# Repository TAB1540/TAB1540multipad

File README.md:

# TAB1540multipad

TAB1540multipad is a 9 key macropad with 1 rotary encoder, an OLED Display. It also has 4 WS2812B Leds, and uses KMK firmware.

## Features

- Basic abs 3d printable case
- 128x32 OLED Display
- 1 EC11 Rotary encoder for spinning around
- 4 WS2812B RGB LEDs.
- 9 keys

## CAD demo

Everything fits together using 4 M3 Bolts. 
Case is made from 2 parts.

Designed using freeCAD 1.0.1 (first time for me)
## PCB

This is my PCB, which was made in KiCad.

PCB

Schematic

## Firmware Overview

This hackpad uses KMK firmware for maybe everything

- The rotary encoder changes volume. press do nothing
- The 9 keys is just keys
- The OLED is something I forgor

## BOM:

Here should be everything you need to make this hackpad

- 9x Cherry MX Switches
- 9x DSA Keycaps
- 4x M3x16mm SHCS Bolts
- 9x 1N4148 DO-35 Diodes.
- 4x WS2812B LEDs
- 1x 0.91" 128x32 OLED Display
- 1x EC11 Rotary Encoder
- 1x XIAO RP2040
- 1x Case (2 printed parts)
## Extra

This is another version of this project

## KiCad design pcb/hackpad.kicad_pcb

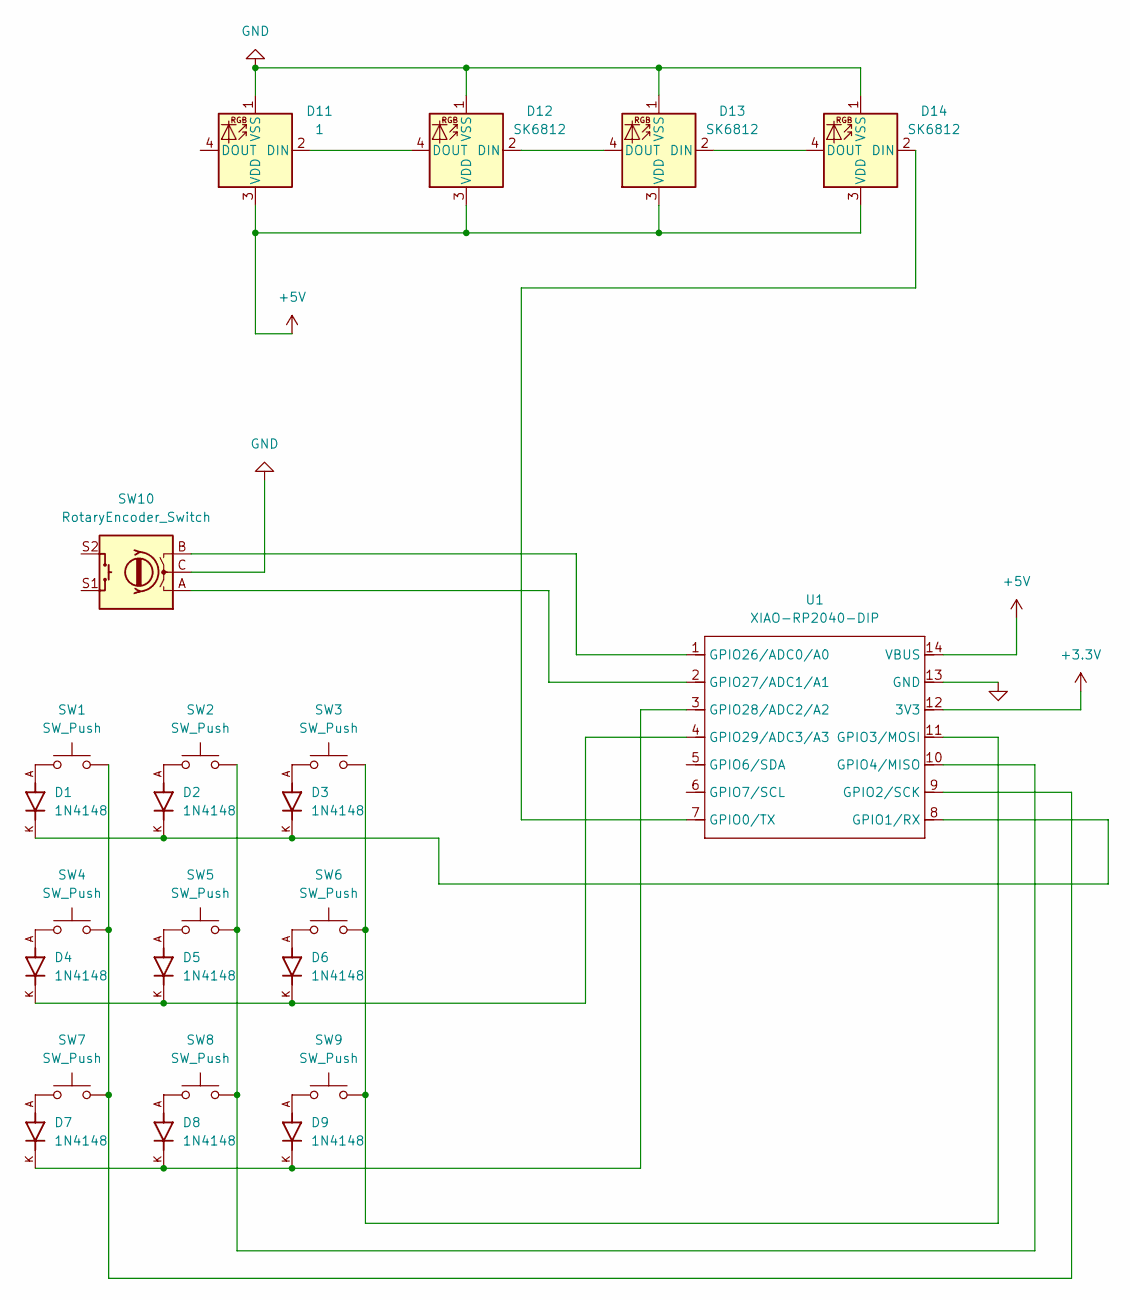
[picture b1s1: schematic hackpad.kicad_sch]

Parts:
D1, D2, D3, D4, D5, D6, D7, D8, D9: 1N4148; DIOAD753W49L380D172B; PARTREV 5
D11: 1; LED_SK6812MINI_PLCC4_3.5x3.5mm_P1.75mm
D12, D13, D14: SK6812; LED_SK6812MINI_PLCC4_3.5x3.5mm_P1.75mm
SW1, SW2, SW3, SW4, SW5, SW6, SW7, SW8, SW9: SW_Push; SW_Cherry_MX_1.00u_PCB
SW10: RotaryEncoder_Switch
U1: XIAO-RP2040-DIP

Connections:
+3.3V: U1.12 (3V3)
+5V: D11.3 (VDD), D12.3 (VDD), D13.3 (VDD), D14.3 (VDD), U1.14 (VBUS)
GND: D11.1 (VSS), D12.1 (VSS), D13.1 (VSS), D14.1 (VSS), SW10.C, U1.13 (GND)
unnamed: D1.A, SW1.1
unnamed: D2.A, SW2.1
unnamed: D3.A, SW3.1
unnamed: D4.A, SW4.1
unnamed: D5.A, SW5.1
unnamed: D6.A, SW6.1
unnamed: D7.A, SW7.1
unnamed: D8.A, SW8.1
unnamed: D9.A, SW9.1
unnamed: D11.2 (DIN), D12.4 (DOUT)
unnamed: D12.2 (DIN), D13.4 (DOUT)
unnamed: D13.2 (DIN), D14.4 (DOUT)
unnamed: D14.2 (DIN), U1.7 (GPIO0/TX)
unnamed: D1.K, D2.K, D3.K, U1.8 (GPIO1/RX)
unnamed: SW1.2, SW4.2, SW7.2, U1.9 (GPIO2/SCK)
unnamed: SW3.2, SW6.2, SW9.2, U1.11 (GPIO3/MOSI)
unnamed: SW2.2, SW5.2, SW8.2, U1.10 (GPIO4/MISO)
unnamed: SW10.B, U1.1 (GPIO26/ADC0/A0)
unnamed: SW10.A, U1.2 (GPIO27/ADC1/A1)
unnamed: D7.K, D8.K, D9.K, U1.3 (GPIO28/ADC2/A2)
unnamed: D4.K, D5.K, D6.K, U1.4 (GPIO29/ADC3/A3)

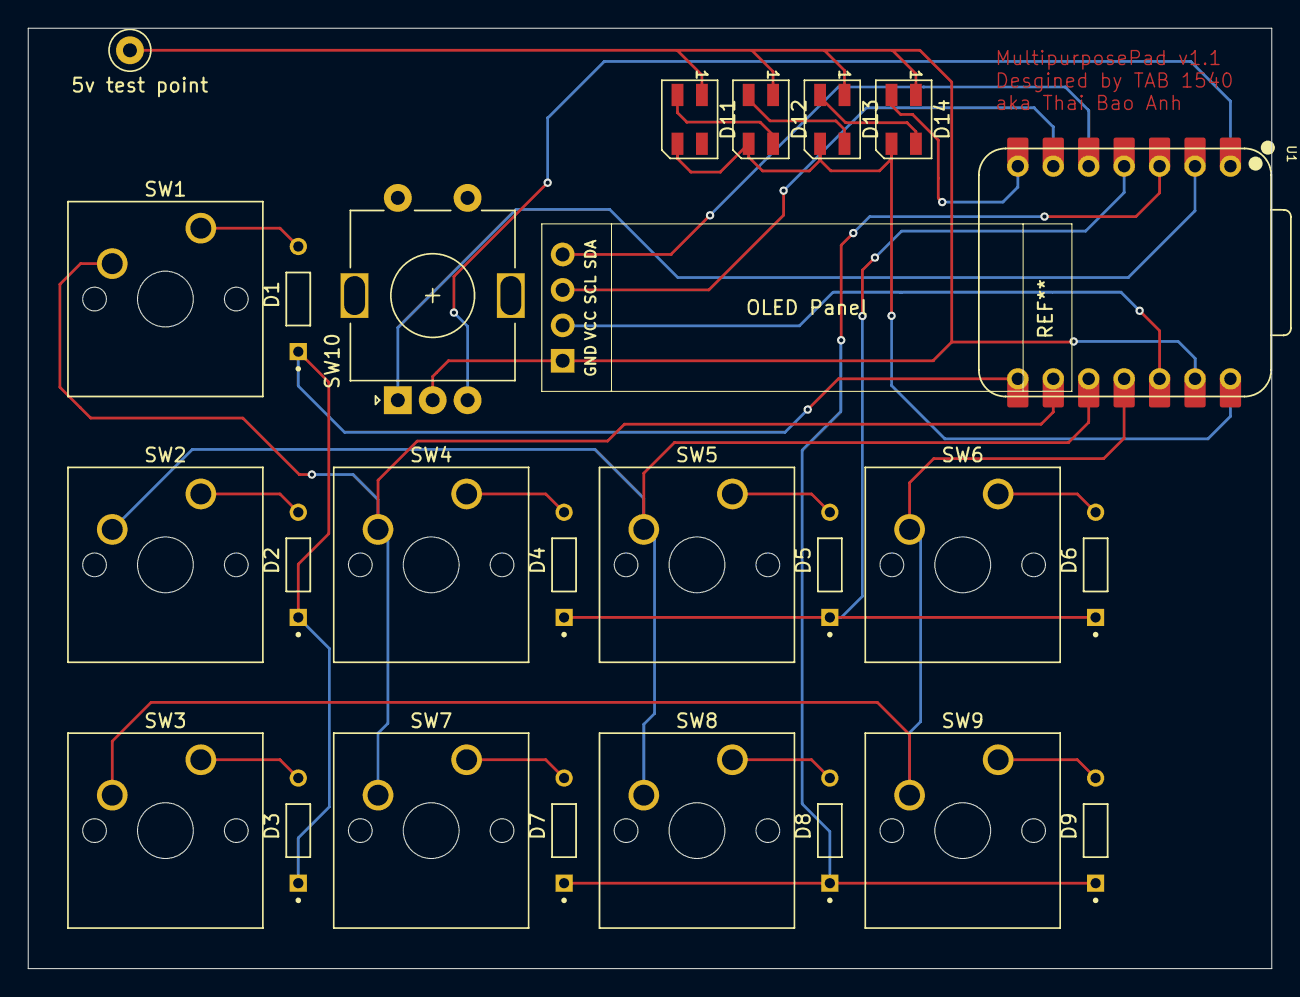
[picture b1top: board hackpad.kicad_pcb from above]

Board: 2 copper layers, 89.1 x 67.4 mm, 25 parts (0 on the bottom side), 23 nets.

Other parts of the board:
5v test point: TestPoint_Loop_D1.80mm_Drill1.0mm_Beaded
